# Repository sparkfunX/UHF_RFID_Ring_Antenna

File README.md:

UHF RFID Ring Antenna
=============================

A small ring antenna for use with Ultra-small UHF RFID tags

Repository Contents
-------------------

* **/Documents** - Documentation
* **/Hardware** - Eagle design files (.brd, .sch)

License Information
-------------------

This product is _**open source**_! 

Please review the LICENSE.md file for license information. 

If you have any questions or concerns on licensing, please contact technical support on our [SparkFun forums](https://forum.sparkfun.com/viewforum.php?f=152).

Distributed as-is; no warranty is given.

- Your friends at SparkFun.

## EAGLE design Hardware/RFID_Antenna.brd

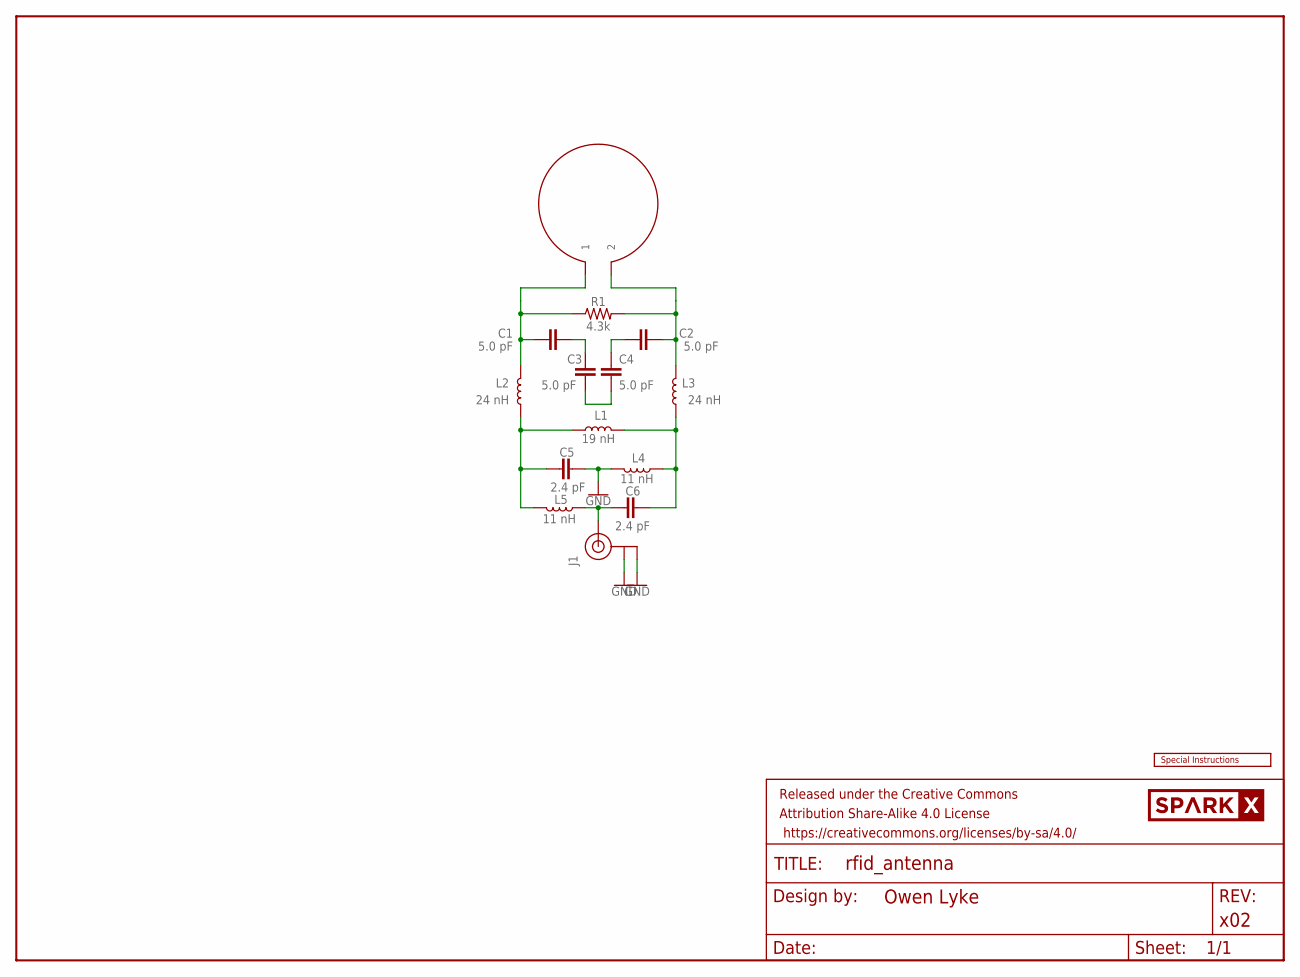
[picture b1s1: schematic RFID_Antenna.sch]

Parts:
C1, C2, C3, C4: 5.0 pF; 0402_MURATA
C5, C6: 2.4 pF; 0402_MURATA
FRAME1: FRAME-LETTER; CREATIVE_COMMONS
J1: U.FL
L1: 19 nH; 0402_MURATA
L2, L3: 24 nH; 0603_MURATA
L4, L5: 11 nH; 0603_MURATA
R1: 4.3k; 0402_MURATA
U$1: ANTENNA; ANT
U$2: SPECIAL_INSTRUCTIONS-ORDERING; ORDERING_INSTRUCTIONS
U$12: SPARKX-LOGO5; SPARKX-LARGE

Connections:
A1: C1.P$1 (1), L2.P$2 (2), R1.P$1 (1), U$1.P$1 (1), U$1.P$3 (1)
A2: C2.P$2 (2), L3.P$2 (2), R1.P$2 (2), U$1.P$2 (2), U$1.P$4 (2)
C1C3: C1.P$2 (2), C3.P$1 (1)
C2C4: C2.P$1 (1), C4.P$1 (1)
C3C4: C3.P$2 (2), C4.P$2 (2)
GND: C5.P$1 (1), J1.1 (GND), J1.2 (GND), L4.P$2 (2)
L5C6: C6.P$2 (2), J1.FEED (SIGNAL), L5.P$1 (1)
unnamed: C6.P$1 (1), L1.P$2 (2), L3.P$1 (1), L4.P$1 (1)
unnamed: C5.P$2 (2), L1.P$1 (1), L2.P$1 (1), L5.P$2 (2)

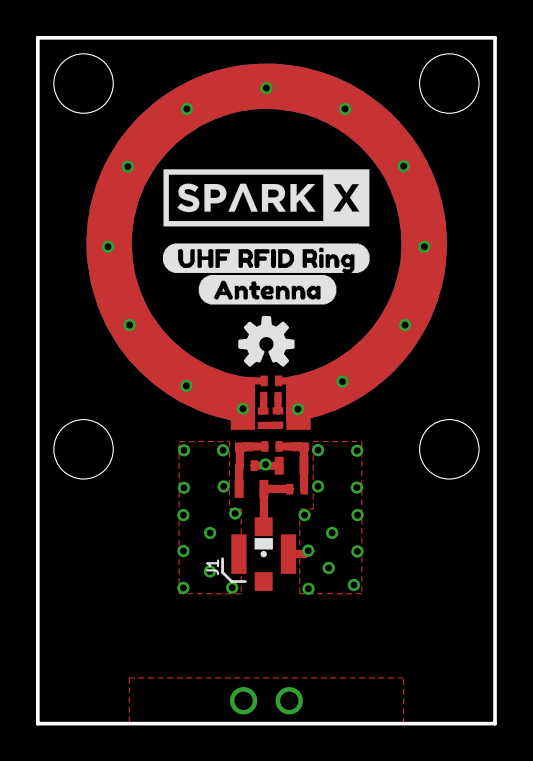
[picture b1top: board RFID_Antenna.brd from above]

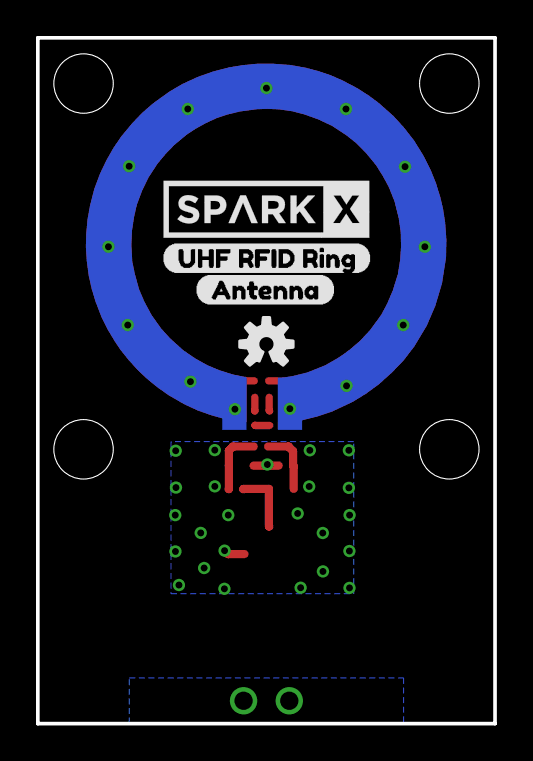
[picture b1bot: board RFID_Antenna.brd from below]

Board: 2 copper layers, 25.4 x 38.1 mm, 25 parts (5 on the bottom side), 9 nets.

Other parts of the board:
U$4: SPARKX-LARGE
U$5, U$6: UHF_RFID_RING0
U$7, U$8: ANTENNA1
U$9, U$10: OSHW-LOGO-S
U$11: QWIIC_BOARD_MOUNT_HOLES

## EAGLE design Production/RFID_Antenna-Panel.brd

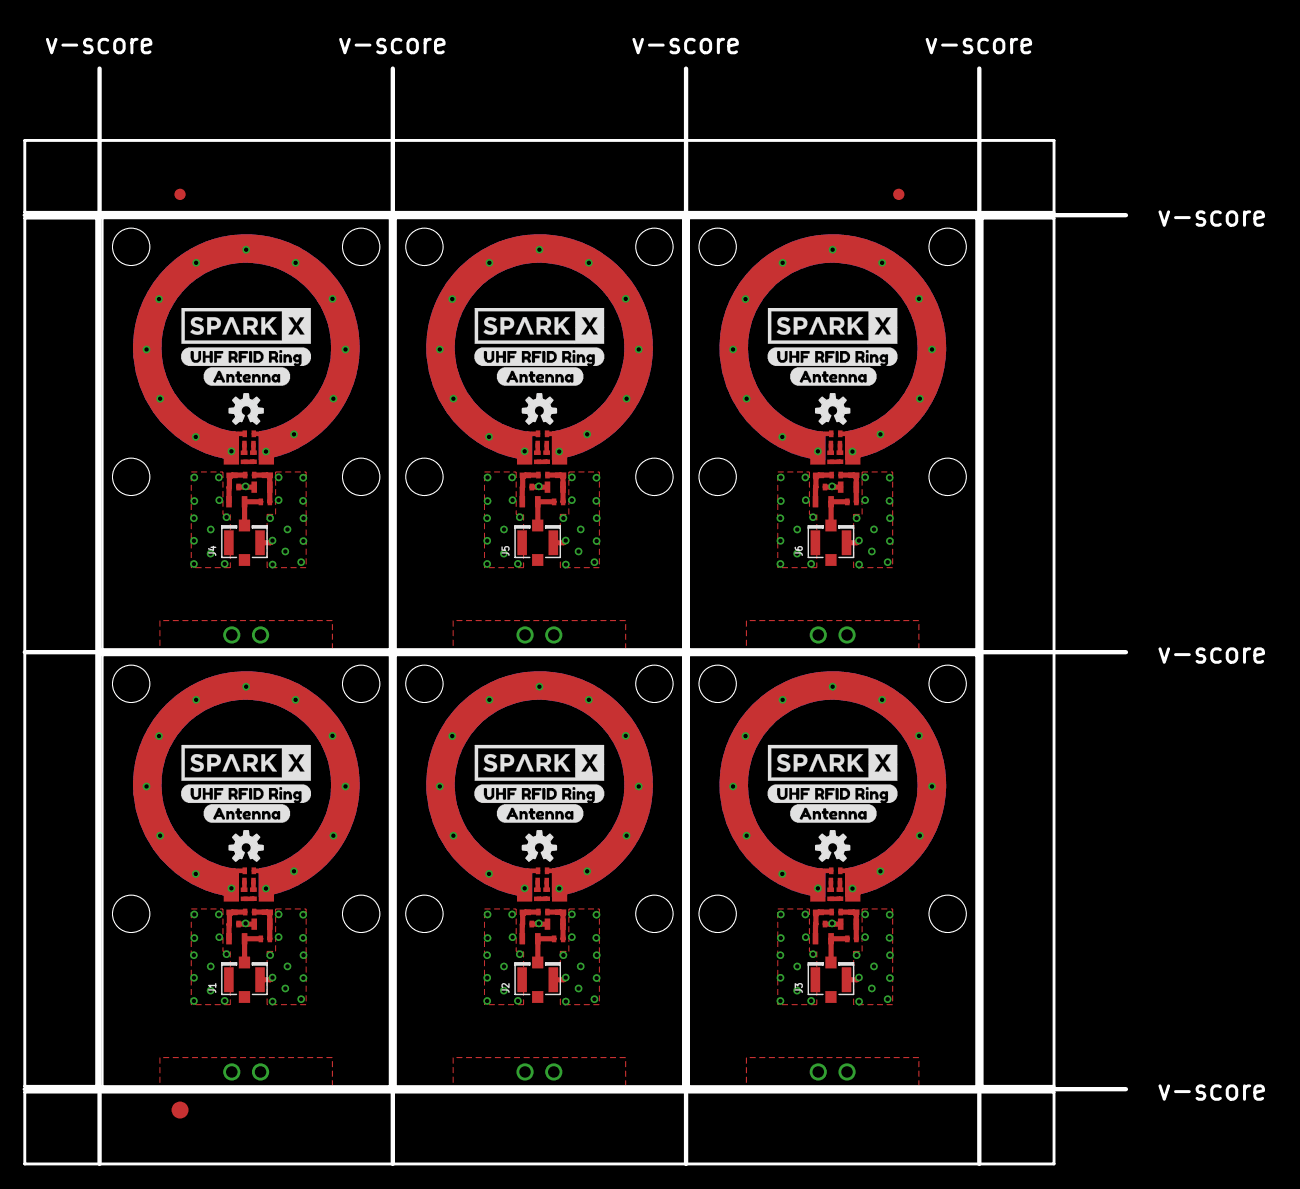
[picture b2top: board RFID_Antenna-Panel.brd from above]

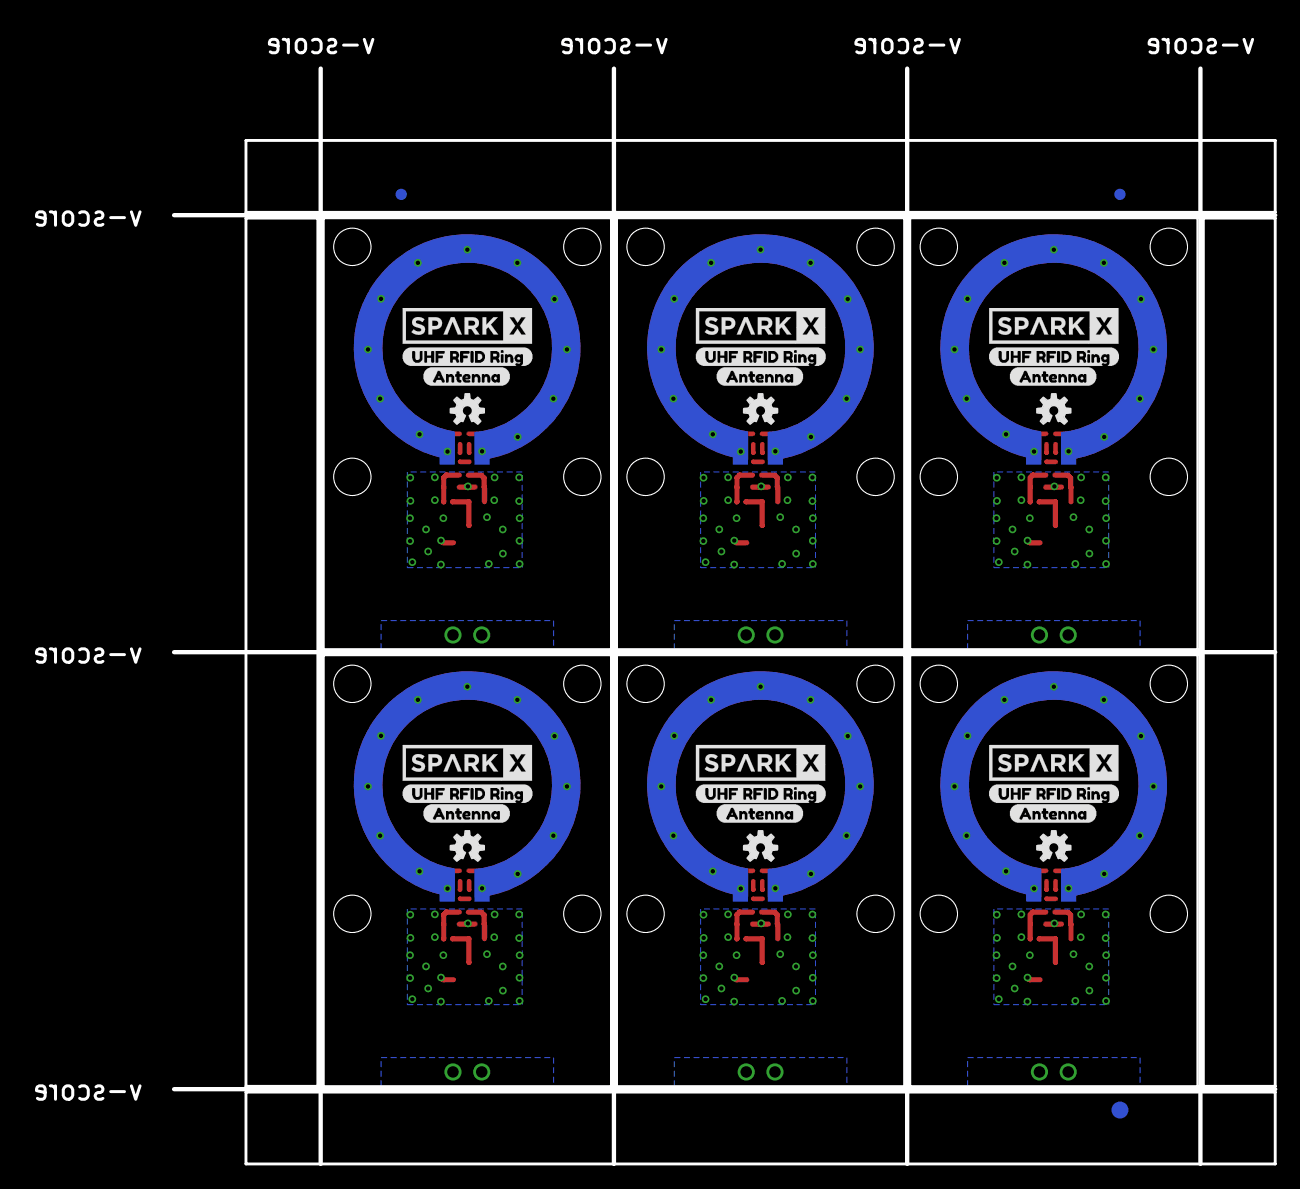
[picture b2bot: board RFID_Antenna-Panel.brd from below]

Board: 2 copper layers, 97.3 x 96.8 mm, 156 parts (33 on the bottom side), 54 nets.

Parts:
C1, C2, C3, C4, C7, C8, C9, C10, C13, C14, C15, C16, C19, C20, C21, C22, C25, C26, C27, C28, C31, C32, C33, C34: 5.0 pF; 0402_MURATA
C5, C6, C11, C12, C17, C18, C23, C24, C29, C30, C35, C36: 2.4 pF; 0402_MURATA
E$1, E$2, E$3, E$4: FIDUCIAL-1X2
E$5, E$6: FIDUCIAL-1.5X3
FRAME1, FRAME2, FRAME3, FRAME4, FRAME5, FRAME6: FRAME-LETTER; CREATIVE_COMMONS
J1, J2, J3, J4, J5, J6: U.FL
L1, L6, L11, L16, L21, L26: 19 nH; 0402_MURATA
L2, L3, L7, L8, L12, L13, L17, L18, L22, L23, L27, L28: 24 nH; 0603_MURATA
L4, L5, L9, L10, L14, L15, L19, L20, L24, L25, L29, L30: 11 nH; 0603_MURATA
R1, R2, R3, R4, R5, R6: 4.28k; 0402_MURATA
U$1, U$2, U$23, U$34, U$45, U$56: ANTENNA; ANT
U$3, U$4, U$13, U$14, U$24, U$25, U$35, U$36, U$46, U$47, U$57, U$58: SPARKX-LARGE
U$5, U$6, U$15, U$16, U$26, U$27, U$37, U$38, U$48, U$49, U$59, U$60: UHF_RFID_RING0
U$7, U$8, U$17, U$18, U$28, U$29, U$39, U$40, U$50, U$51, U$61, U$62: ANTENNA1
U$9, U$10, U$19, U$20, U$30, U$31, U$41, U$42, U$52, U$53, U$63, U$64: OSHW-LOGO-S
U$11, U$21, U$32, U$43, U$54, U$65: QWIIC_BOARD_MOUNT_HOLES
U$12, U$22, U$33, U$44, U$55, U$66: SPARKX-LOGO6; SPARKX-XLARGE

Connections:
A1: C1.P$1, L2.P$2, R1.P$1, U$1.P$1, U$1.P$3
A2: C2.P$2, L3.P$2, R1.P$2, U$1.P$2, U$1.P$4
A3: C7.P$1, L7.P$2, R2.P$1, U$2.P$1, U$2.P$3
A4: C8.P$2, L8.P$2, R2.P$2, U$2.P$2, U$2.P$4
A5: C13.P$1, L12.P$2, R3.P$1, U$23.P$1, U$23.P$3
A6: C14.P$2, L13.P$2, R3.P$2, U$23.P$2, U$23.P$4
A7: C19.P$1, L17.P$2, R4.P$1, U$34.P$1, U$34.P$3
A8: C20.P$2, L18.P$2, R4.P$2, U$34.P$2, U$34.P$4
A9: C25.P$1, L22.P$2, R5.P$1, U$45.P$1, U$45.P$3
A10: C26.P$2, L23.P$2, R5.P$2, U$45.P$2, U$45.P$4
A11: C31.P$1, L27.P$2, R6.P$1, U$56.P$1, U$56.P$3
A12: C32.P$2, L28.P$2, R6.P$2, U$56.P$2, U$56.P$4
C1C1: C7.P$2, C9.P$1
C1C2: C13.P$2, C15.P$1
C1C3: C1.P$2, C3.P$1
C1C4: C19.P$2, C21.P$1
C1C5: C25.P$2, C27.P$1
C1C6: C31.P$2, C33.P$1
C2C1: C8.P$1, C10.P$1
C2C2: C14.P$1, C16.P$1
C2C3: C20.P$1, C22.P$1
C2C4: C2.P$1, C4.P$1
C2C5: C26.P$1, C28.P$1
C2C6: C32.P$1, C34.P$1
C3C1: C9.P$2, C10.P$2
C3C2: C15.P$2, C16.P$2
C3C3: C21.P$2, C22.P$2
C3C4: C3.P$2, C4.P$2
C3C5: C27.P$2, C28.P$2
C3C6: C33.P$2, C34.P$2
GND: C5.P$1, J1.1, J1.2, L4.P$2
GND2: C11.P$1, J2.1, J2.2, L9.P$2
GND4: C17.P$1, J3.1, J3.2, L14.P$2
GND6: C23.P$1, J4.1, J4.2, L19.P$2
GND8: C29.P$1, J5.1, J5.2, L24.P$2
GND10: C35.P$1, J6.1, J6.2, L29.P$2
L5C1: C12.P$2, J2.FEED, L10.P$1
L5C2: C18.P$2, J3.FEED, L15.P$1
L5C3: C24.P$2, J4.FEED, L20.P$1
L5C4: C30.P$2, J5.FEED, L25.P$1
L5C5: C36.P$2, J6.FEED, L30.P$1
L5C6: C6.P$2, J1.FEED, L5.P$1
unnamed: C12.P$1, L6.P$2, L8.P$1, L9.P$1
unnamed: C11.P$2, L6.P$1, L7.P$1, L10.P$2
unnamed: C6.P$1, L1.P$2, L3.P$1, L4.P$1
unnamed: C5.P$2, L1.P$1, L2.P$1, L5.P$2
unnamed: C18.P$1, L11.P$2, L13.P$1, L14.P$1
unnamed: C17.P$2, L11.P$1, L12.P$1, L15.P$2
unnamed: C24.P$1, L16.P$2, L18.P$1, L19.P$1
unnamed: C23.P$2, L16.P$1, L17.P$1, L20.P$2
unnamed: C30.P$1, L21.P$2, L23.P$1, L24.P$1
unnamed: C29.P$2, L21.P$1, L22.P$1, L25.P$2
unnamed: C36.P$1, L26.P$2, L28.P$1, L29.P$1
unnamed: C35.P$2, L26.P$1, L27.P$1, L30.P$2

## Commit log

2018-12-20 Caopy Murata Design w/ Transparency for x02
2019-01-08 Add production for x02
2019-01-14 Prettified schematic (and fixed component values)
2019-03-18 Updated production to match single file
    * Updated component values were not reflected in production file
    * Ran panelization script on correct board
2019-03-25 Updated parts with PROD_ID and Eagle Library for production
2019-03-25 Linked SparkX logo between schematic and brd
2019-03-26 Re-org files
2019-03-26 Add tValue
2019-03-26 Added tvalues for production
2020-11-23 Add README and license

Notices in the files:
parts and their libraries:
SparkFun-Aesthetics: Licensing: Creative Commons ShareAlike 4.0 International - https://creativecommons.org/licenses/by-sa/4.0
SparkFun-Aesthetics: Released under the Creative Commons Attribution Share-Alike 4.0 License
SparkFun-Aesthetics: https://creativecommons.org/licenses/by-sa/4.0
